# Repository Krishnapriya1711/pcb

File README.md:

# Plug-and-Play Robotic Controller PCB (Teensy 4.1)

This repository contains the schematic and PCB design files for a plug-and-play microcontroller-based control board built around the Teensy 4.1, developed for robotic applications.

## Overview
The PCB is designed as a reusable control unit centered on the Teensy 4.1 microcontroller. Using standardized header pin slots, the board can be easily integrated into different robotic platforms, including robotic arms and mobile chassis, without requiring hardware redesign.

The design emphasizes modularity, flexibility, and ease of integration, allowing the same controller board to be reused across multiple robotic systems.

## Key Features
- Plug-and-play controller based on Teensy 4.1
- Header pin slots for easy actuator and sensor connections
- Supports robotic arm, science module and chassis control
- Modular and reusable hardware design
- Power regulation and distribution for control electronics
- Designed using KiCad

## Tools & Technologies
- Teensy 4.1
- KiCad (Schematic & PCB Layout)
- Embedded systems and robotics control architecture

## Repository Contents
- Schematic design files
- PCB layout files
- Board renders / previews
- BOM and Gerber files

## Applications
- Robotic arm control systems
- Mobile robot chassis control
- Embedded robotics prototyping
- Educational robotics platforms

## Design Philosophy
- Hardware reusability across multiple robotic platforms
- Plug-and-play integration using standardized headers
- Simplified wiring, debugging, and expansion

## Future Improvements
- Add protection circuitry (overcurrent, reverse polarity)
- Support additional communication interfaces
- Further miniaturization and optimization

This is the 3D preview of the board

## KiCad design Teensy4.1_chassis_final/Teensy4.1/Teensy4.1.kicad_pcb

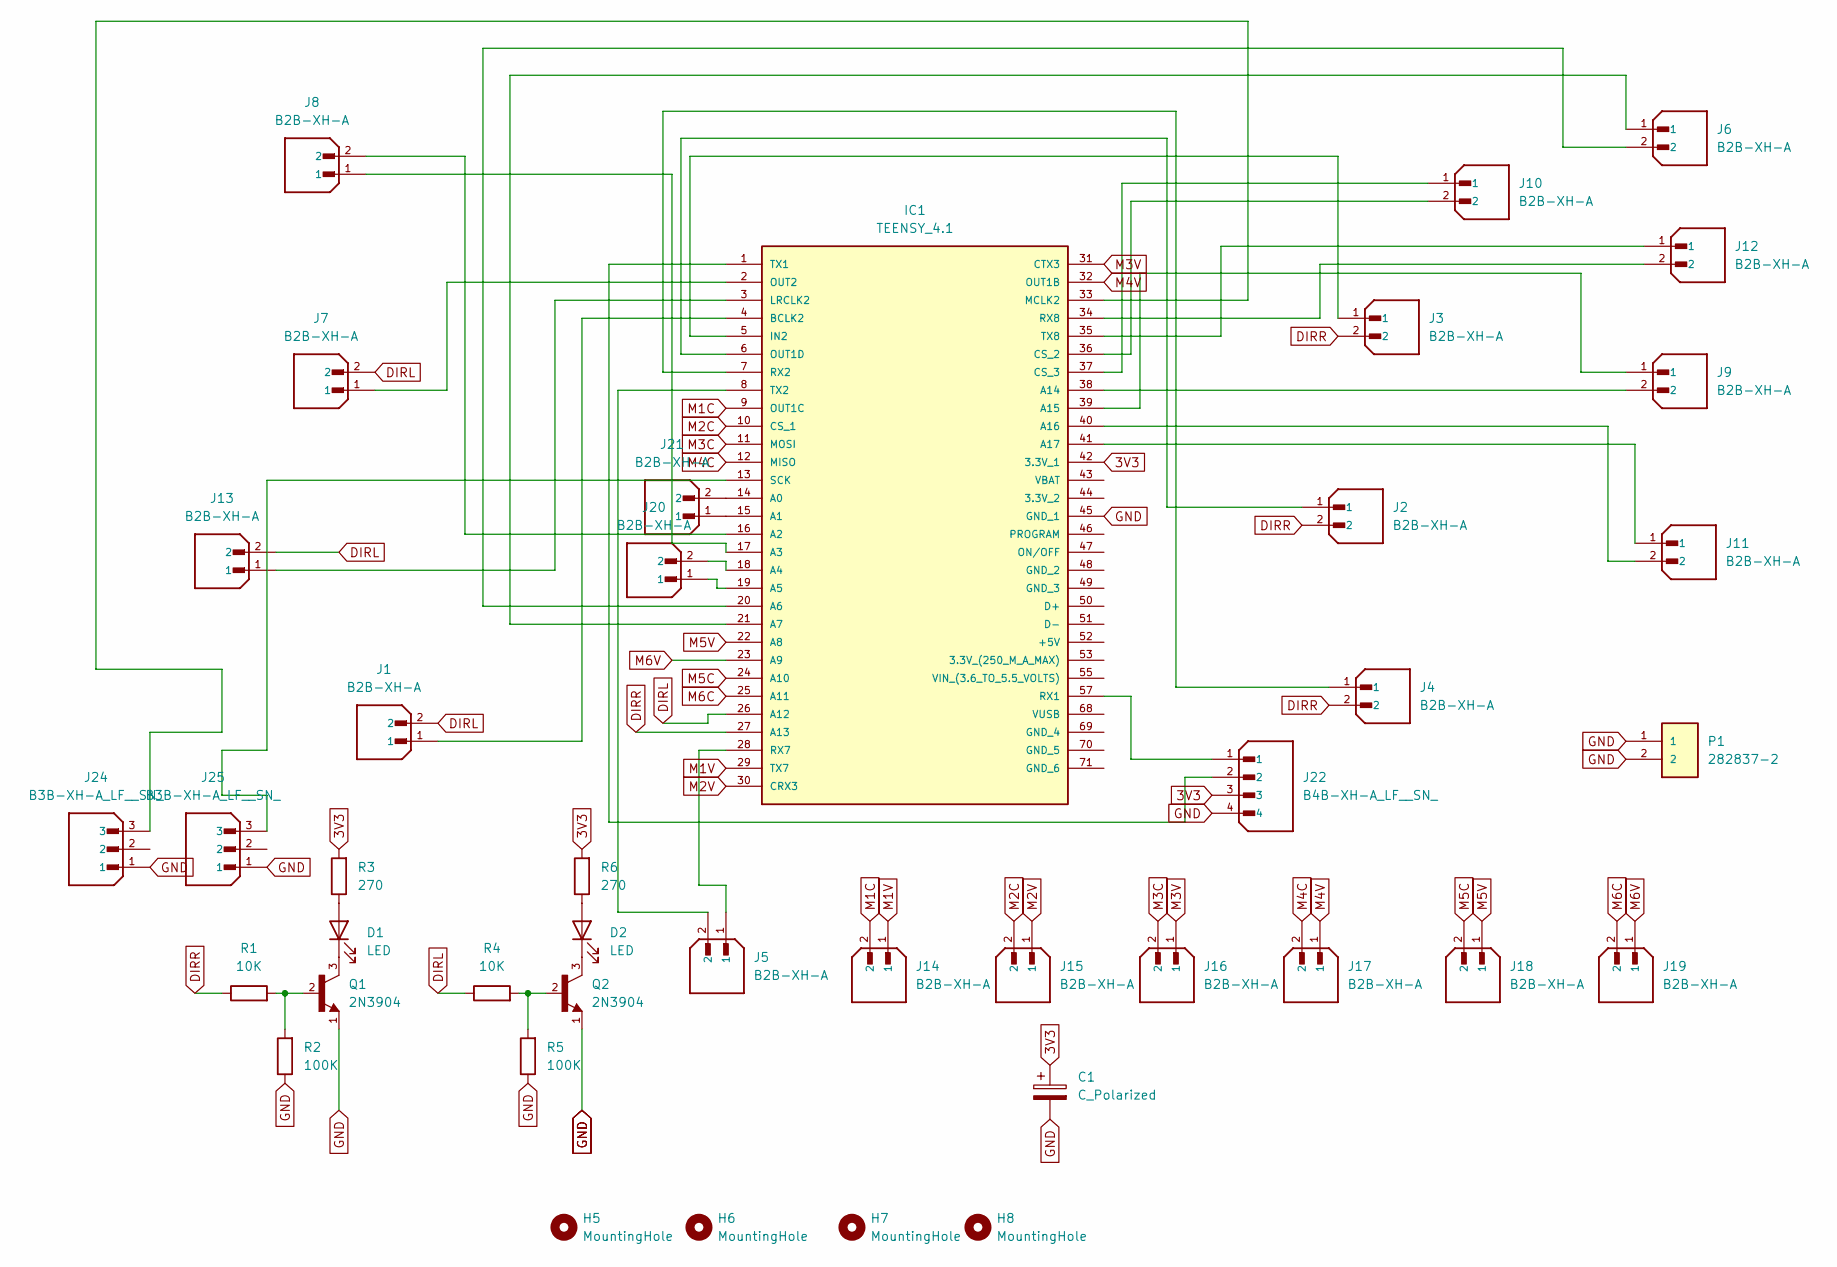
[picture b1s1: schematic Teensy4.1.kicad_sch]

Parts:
C1: C_Polarized; CP_Radial_D8.0mm_P5.00mm
D1, D2: LED; LED_D3.0mm_Horizontal_O1.27mm_Z6.0mm
H5, H6, H7, H8: MountingHole; MountingHole_3mm_Pad_TopBottom
IC1: TEENSY_4.1; TEENSY41; Manufacturer_Part_Number TEENSY 4.1
J1, J2, J3, J4, J5, J6, J7, J8, J9, J10, J11, J12, J13, J14, J15, J16, J17, J18, J19, J20, J21: B2B-XH-A; JST_XH_B2B-XH-A_1x02_P2.50mm_Vertical; PARTREV N/A
J22: B4B-XH-A_LF__SN_; JST_B4B-XH-A_LF__SN_; PARTREV 7/4/21
J24, J25: B3B-XH-A_LF__SN_; JST_B3B-XH-A; PARTREV 7/4/21
P1: 282837-2; TE_282837-2; PARTREV G3
Q1, Q2: 2N3904; TO92127P495H495-3_modified; PARTREV February 2003
R1, R4: 10K; R_Axial_DIN0207_L6.3mm_D2.5mm_P7.62mm_Horizontal
R2, R5: 100K; R_Axial_DIN0207_L6.3mm_D2.5mm_P7.62mm_Horizontal
R3, R6: 270; R_Axial_DIN0207_L6.3mm_D2.5mm_P7.62mm_Horizontal

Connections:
3V3: C1.1, IC1.42 (3.3V_1), J22.3, R3.2, R6.2
DIRL: IC1.26 (A12), J1.2, J7.2, J13.2, R4.1
DIRR: IC1.27 (A13), J2.2, J3.2, J4.2, R1.1
GND: C1.2, IC1.45 (GND_1), J22.4, J24.1, J25.1, P1.1, P1.2, Q1.1, Q2.1, R2.1, R5.1
M1C: IC1.9 (OUT1C), J14.2
M1V: IC1.29 (TX7), J14.1
M2C: IC1.10 (CS_1), J15.2
M2V: IC1.30 (CRX3), J15.1
M3C: IC1.11 (MOSI), J16.2
M3V: IC1.31 (CTX3), J16.1
M4C: IC1.12 (MISO), J17.2
M4V: IC1.32 (OUT1B), J17.1
M5C: IC1.24 (A10), J18.2
M5V: IC1.22 (A8), J18.1
M6C: IC1.25 (A11), J19.2
M6V: IC1.23 (A9), J19.1
unnamed: D1.2 (A), R3.1
unnamed: D1.1 (K), Q1.3
unnamed: D2.2 (A), R6.1
unnamed: D2.1 (K), Q2.3
unnamed: IC1.14 (A0), J21.2
unnamed: IC1.15 (A1), J21.1
unnamed: IC1.16 (A2), J8.2
unnamed: IC1.17 (A3), J8.1
unnamed: IC1.18 (A4), J20.2
unnamed: IC1.19 (A5), J20.1
unnamed: IC1.20 (A6), J6.2
unnamed: IC1.21 (A7), J6.1
unnamed: IC1.38 (A14), J9.2
unnamed: IC1.39 (A15), J9.1
unnamed: IC1.40 (A16), J11.2
unnamed: IC1.41 (A17), J11.1
unnamed: IC1.4 (BCLK2), J1.1
unnamed: IC1.36 (CS_2), J10.2
unnamed: IC1.37 (CS_3), J10.1
unnamed: IC1.5 (IN2), J3.1
unnamed: IC1.3 (LRCLK2), J13.1
unnamed: IC1.33 (MCLK2), J24.3
unnamed: IC1.6 (OUT1D), J2.1
unnamed: IC1.2 (OUT2), J7.1
unnamed: IC1.57 (RX1), J22.1
unnamed: IC1.7 (RX2), J4.1
unnamed: IC1.28 (RX7), J5.1
unnamed: IC1.34 (RX8), J12.2
unnamed: IC1.13 (SCK), J25.3
unnamed: IC1.1 (TX1), J22.2
unnamed: IC1.8 (TX2), J5.2
unnamed: IC1.35 (TX8), J12.1
unnamed: Q1.2, R1.2, R2.2
unnamed: Q2.2, R4.2, R5.2

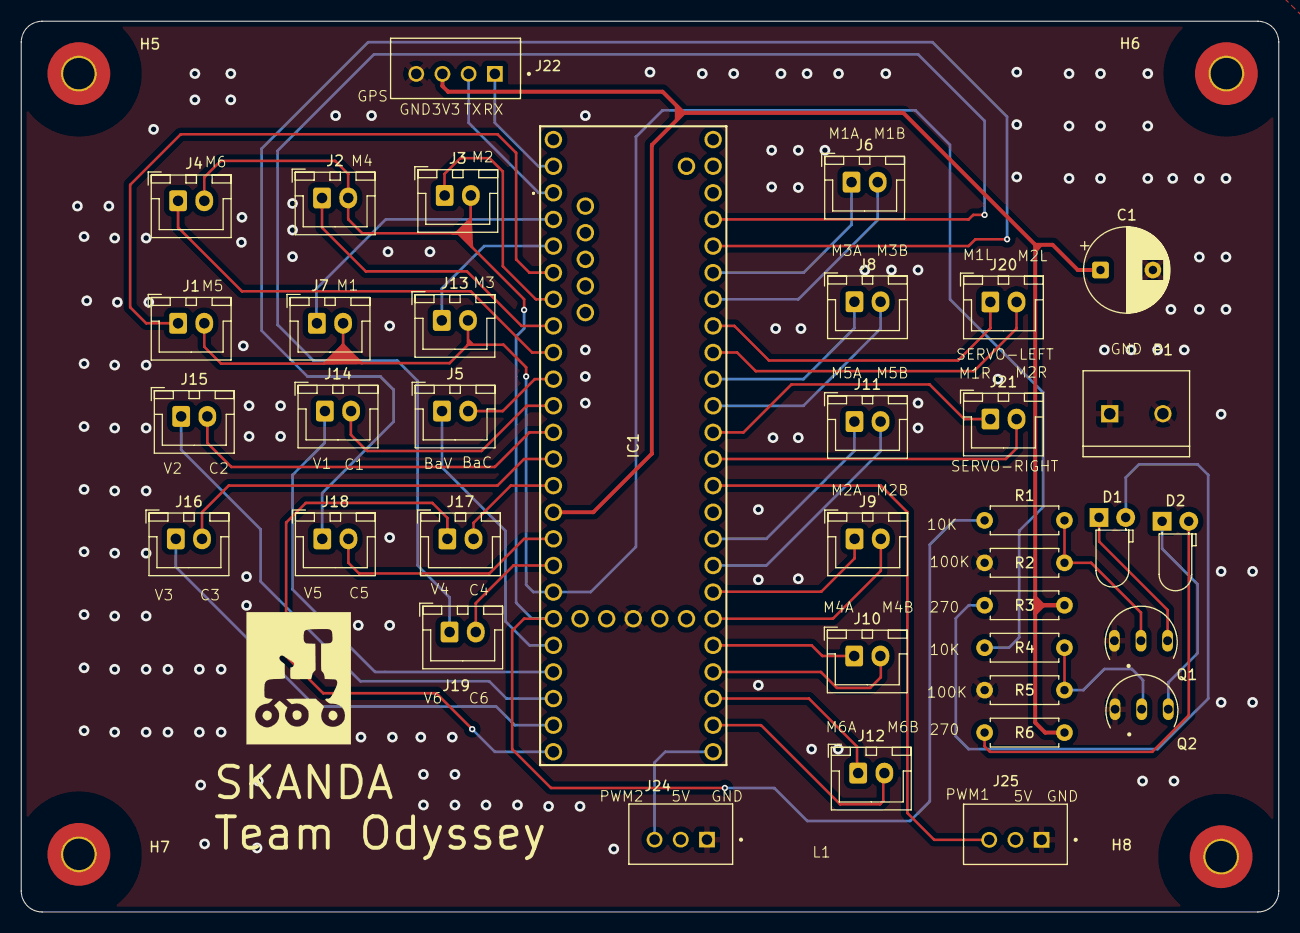
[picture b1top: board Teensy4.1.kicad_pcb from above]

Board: 2 copper layers, 120.0 x 85.0 mm, 41 parts (0 on the bottom side), 50 nets.

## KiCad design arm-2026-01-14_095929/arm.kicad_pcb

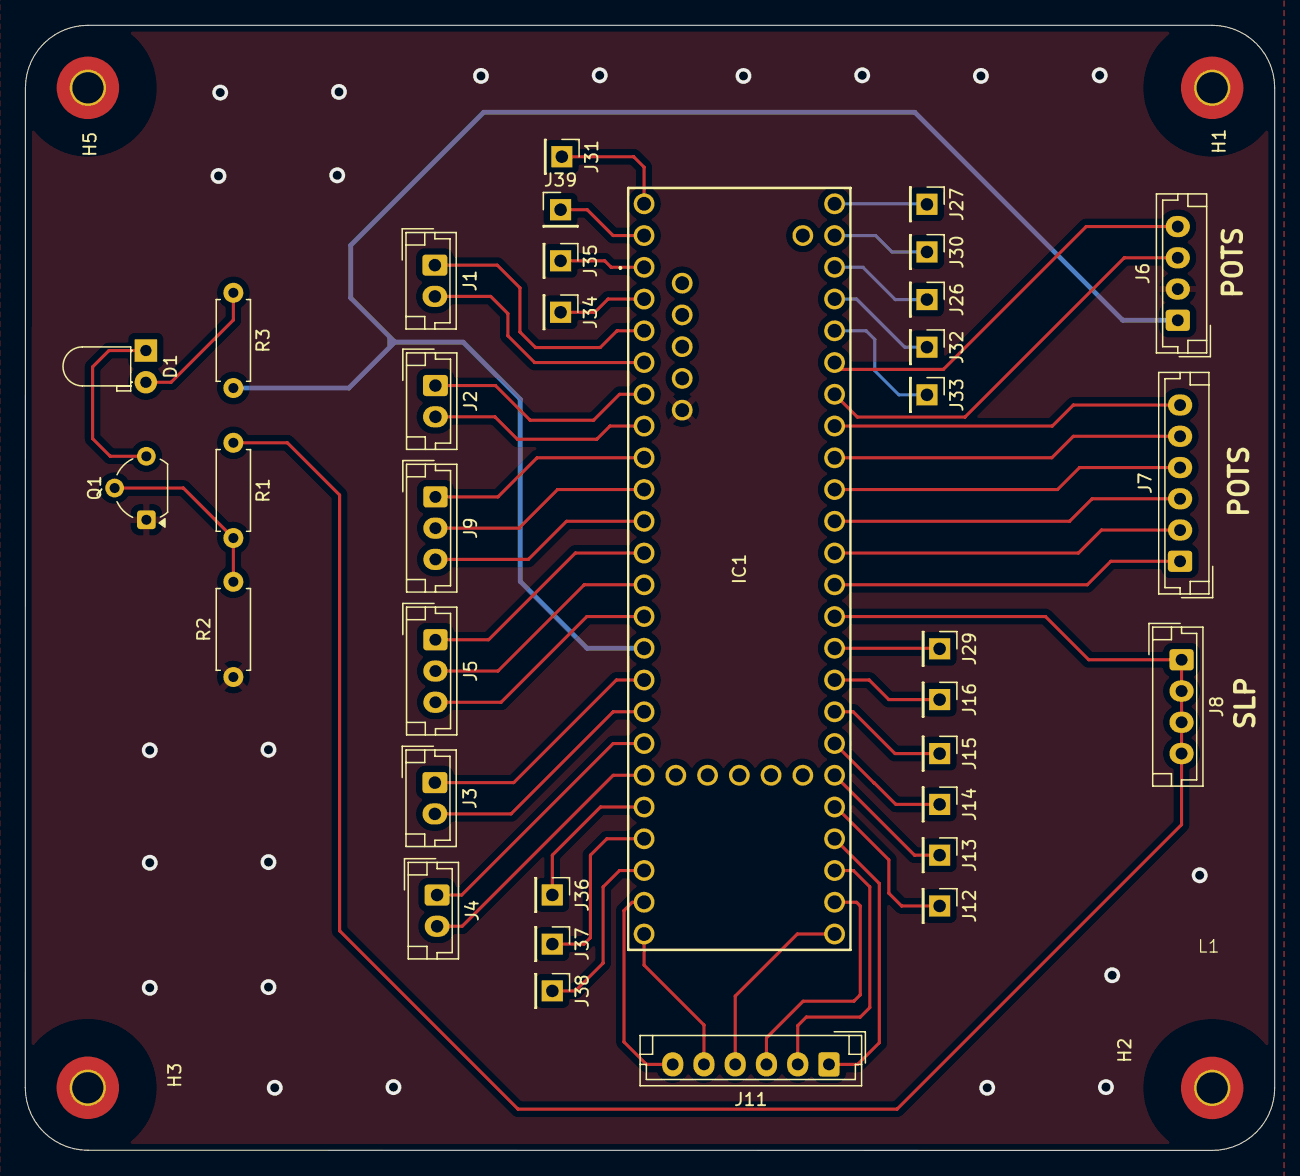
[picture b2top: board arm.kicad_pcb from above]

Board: 2 copper layers, 100.0 x 90.0 mm, 38 parts (0 on the bottom side), 52 nets.

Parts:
D1: LED; LED_D3.0mm_Horizontal_O1.27mm_Z6.0mm
H1, H2, H3, H5: MountingHole; MountingHole_2.5mm_Pad_TopBottom
IC1: TEENSY_4.1; TEENSY41
J1, J2, J3, J4: Conn_01x02_Pin; JST_EH_B2B-EH-A_1x02_P2.50mm_Vertical
J5, J9: Conn_01x03_Pin; JST_EH_B3B-EH-A_1x03_P2.50mm_Vertical
J6, J8: Conn_01x04_Pin; JST_EH_B4B-EH-A_1x04_P2.50mm_Vertical
J7, J11: Conn_01x06_Pin; JST_EH_B6B-EH-A_1x06_P2.50mm_Vertical
J12, J13, J14, J15, J16, J26, J27, J29, J30, J31, J32, J33, J34, J35, J36, J37, J38, J39: Conn_01x01_Pin; PinHeader_1x01_P2.54mm_Vertical
Q1: 2N3904; TO-92L_Wide
R1: 10K; R_Axial_DIN0207_L6.3mm_D2.5mm_P7.62mm_Horizontal
R2: 100K; R_Axial_DIN0207_L6.3mm_D2.5mm_P7.62mm_Horizontal
R3: 270; R_Axial_DIN0207_L6.3mm_D2.5mm_P7.62mm_Horizontal

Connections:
3V3: IC1.42 (3.3V_1), J6.1, R3.2
GND: IC1.48 (GND_2), J6.2, Q1.1, R2.1
unnamed: D1.2 (A), R3.1
unnamed: D1.1 (K), Q1.3
unnamed: IC1.53 (3.3V_(250_M_A_MAX)), J26.1
unnamed: IC1.14 (A0), J7.1
unnamed: IC1.15 (A1), J7.2
unnamed: IC1.16 (A2), J7.3
unnamed: IC1.17 (A3), J7.4
unnamed: IC1.18 (A4), J7.5
unnamed: IC1.19 (A5), J7.6
unnamed: IC1.20 (A6), J6.3
unnamed: IC1.21 (A7), J6.4
unnamed: IC1.22 (A8), J33.1
unnamed: IC1.23 (A9), J32.1
unnamed: IC1.24 (A10), J3.1
unnamed: IC1.25 (A11), J3.2
unnamed: IC1.26 (A12), J4.1
unnamed: IC1.27 (A13), J4.2
unnamed: IC1.38 (A14), J13.1
unnamed: IC1.39 (A15), J14.1
unnamed: IC1.40 (A16), J15.1
unnamed: IC1.41 (A17), J16.1
unnamed: IC1.4 (BCLK2), J1.2
unnamed: IC1.30 (CRX3), J38.1
unnamed: IC1.10 (CS_1), J5.1
unnamed: IC1.36 (CS_2), J11.1
unnamed: IC1.37 (CS_3), J12.1
unnamed: IC1.31 (CTX3), J11.6
unnamed: IC1.69 (GND_4), J29.1
unnamed: IC1.70 (GND_5), J30.1
unnamed: IC1.71 (GND_6), J31.1
unnamed: IC1.5 (IN2), J2.1
unnamed: IC1.3 (LRCLK2), J1.1
unnamed: IC1.33 (MCLK2), J11.4
unnamed: IC1.12 (MISO), J5.3
unnamed: IC1.11 (MOSI), J5.2
unnamed: IC1.32 (OUT1B), J11.5
unnamed: IC1.9 (OUT1C), J9.3
unnamed: IC1.6 (OUT1D), J2.2
unnamed: IC1.2 (OUT2), J34.1
unnamed: IC1.57 (RX1), J39.1
unnamed: IC1.7 (RX2), J9.1
unnamed: IC1.28 (RX7), J36.1
unnamed: IC1.34 (RX8), J11.3
unnamed: IC1.1 (TX1), J35.1
unnamed: IC1.8 (TX2), J9.2
unnamed: IC1.29 (TX7), J37.1
unnamed: IC1.35 (TX8), J11.2
unnamed: IC1.55 (VIN_(3.6_TO_5.5_VOLTS)), J27.1
unnamed: Q1.2, R1.2, R2.2
SLP: IC1.13 (SCK), J8.1, J8.2, J8.3, J8.4, R1.1

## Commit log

2026-02-04 Update README.md
    Expanded the README to include detailed project information, features, tools, applications, design philosophy, and future improvements.
2026-02-04 Update README to include science module support
